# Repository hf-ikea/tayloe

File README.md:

### tayloe downmixer
This is a simple I/Q downmixer intended for use with a soundcard for digitization, with one (very poor) revision created in a weekend, after I discovered the existence of Tayloe detectors online. Created under the influence of music (sumic). Iterations have occured, with the recommended version being the latest commit to this repo. As of writing, however, the design has not been tested in real world (but shall eventually be). The current (and likely forever) design uses a FT232H communicating over I2C to a Si5351A that is then used in a divide-by-four to create the I/Q paired LO, fed into the multiplexer. On the front end is a simple elliptical LPF with a ~30MHz rolloff, and a 1.8V bias circuit. The sample capacitors are of value 0.068uF, which are on the input of an ADA4084 operational amplifier. This is connected through bypass capacitors to the 3.5mm audio jack. For simplicity, a single rail supply is used for the operational amplifier, as the bias on the input should maintain a proper swing.\
"Inspired" by the classic "A Software Defined Radio for the Masses" Series, published in QEX (and available in this repo).\
Hardware is licensed under CERN Open Hardware Licence Version 2 - Strongly Reciprocal (LICENSE.txt)

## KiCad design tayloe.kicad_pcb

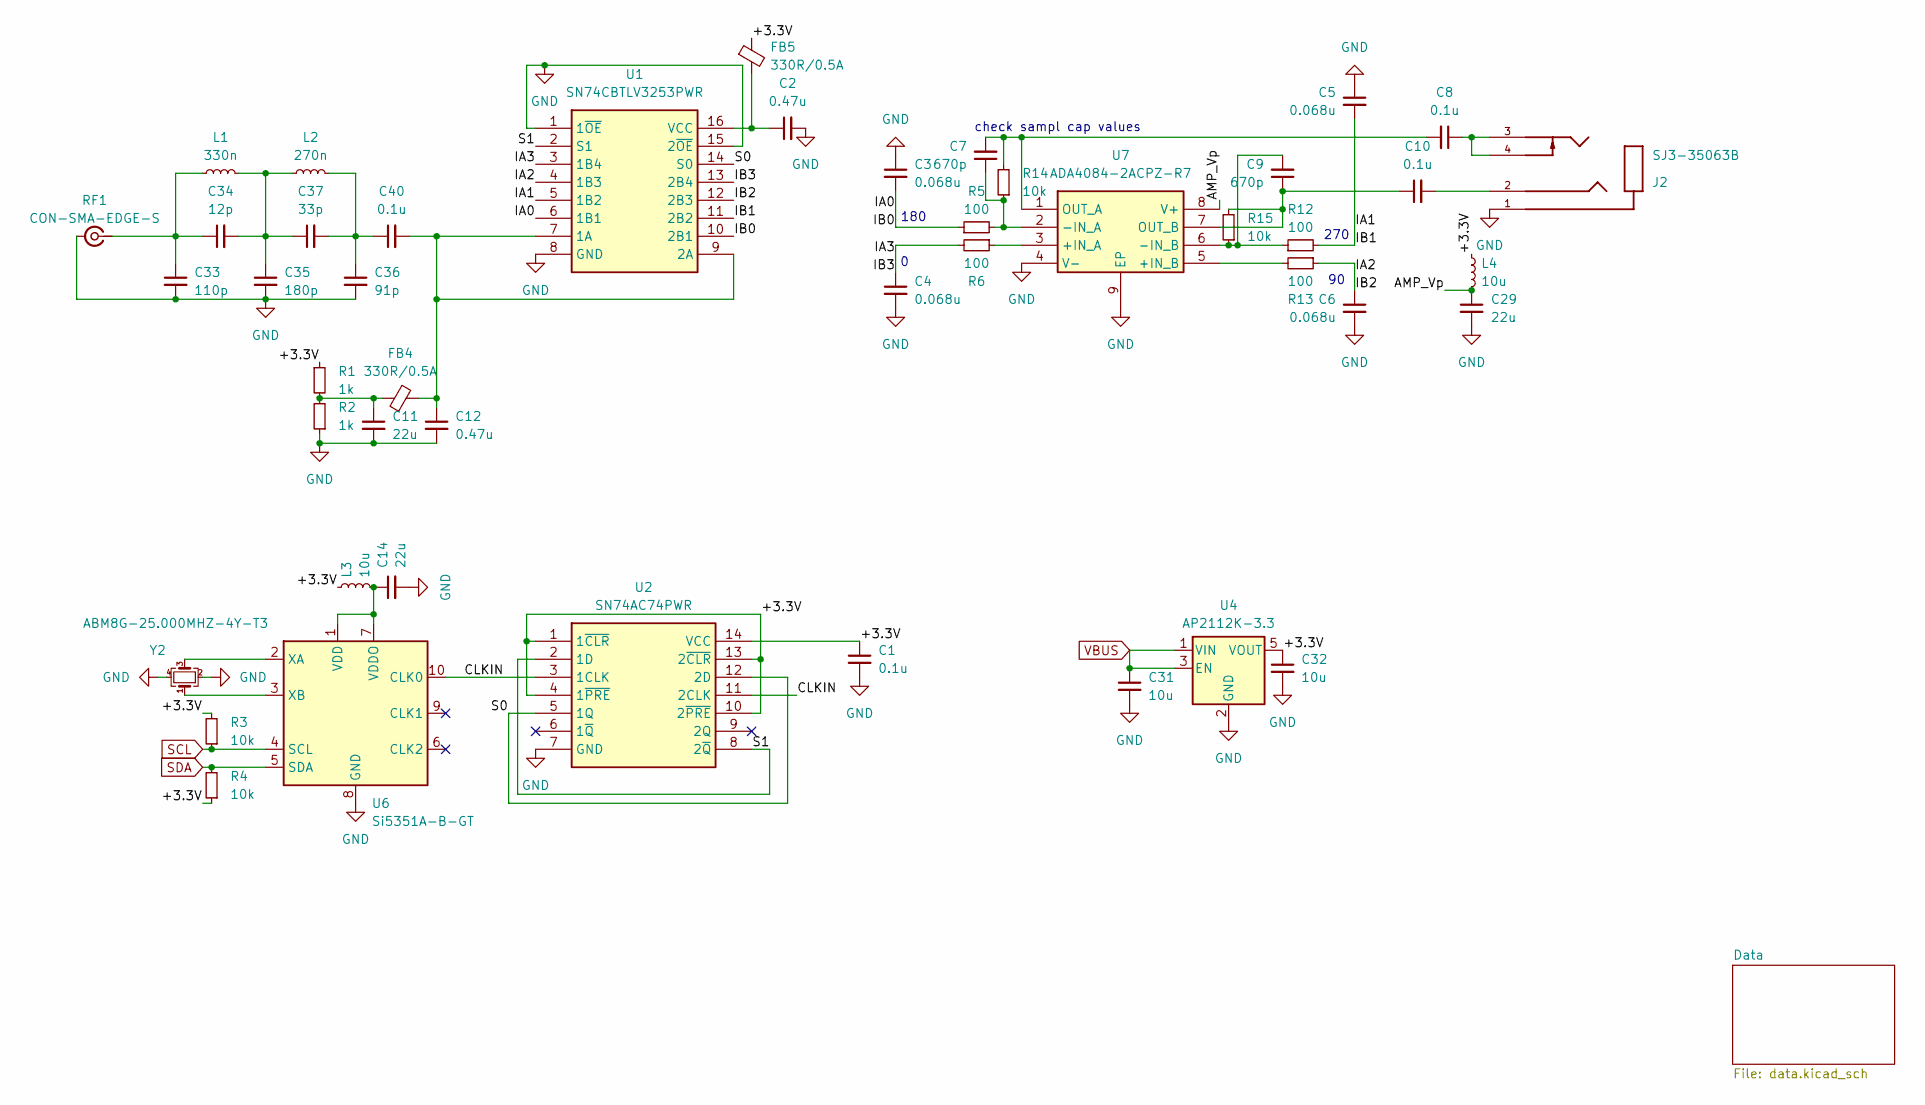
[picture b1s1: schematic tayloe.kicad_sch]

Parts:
C1, C8, C10, C40: 0.1u; C_0603_1608Metric
C2, C12: 0.47u; C_0603_1608Metric
C3, C4, C5, C6: 0.068u; C_0603_1608Metric; Mouser Part 603-CC603JRX7R8BB683
C7, C9: 670p; C_0603_1608Metric; Mouser Part 603-CC603JRX7R8BB683
C11, C14, C29: 22u; C_0603_1608Metric
C31, C32: 10u; C_0603_1608Metric
C33: 110p; C_0603_1608Metric
C34: 12p; C_0603_1608Metric
C35: 180p; C_0603_1608Metric
C36: 91p; C_0603_1608Metric
C37: 33p; C_0603_1608Metric
FB4, FB5: 330R/0.5A; L_0603_1608Metric; Mouser Part 81-BLM18HK331SN1
J2: SJ3-35063B; SAMESKY_SJ3-35063B; PARTREV 1.0
L1: 330n; L_0603_1608Metric
L2: 270n; L_0603_1608Metric
L3, L4: 10u; L_0603_1608Metric
R1, R2: 1k; R_0603_1608Metric
R3, R4, R14, R15: 10k; R_0603_1608Metric
R5, R6, R12, R13: 100; R_0603_1608Metric
RF1: CON-SMA-EDGE-S; SMA_Amphenol_132289_EdgeMount
U1: SN74CBTLV3253PWR; TSSOP-16_4.4x5mm_P0.65mm; Mouser Part 595-SN74CBTLV3253PWR
U2: SN74AC74PWR; TSSOP-14_4.4x5mm_P0.65mm; Mouser Part Number 595-SN74AC74PWR
U4: AP2112K-3.3; SOT-23-5
U6: Si5351A-B-GT; MSOP-10_3x3mm_P0.5mm
U7: ADA4084-2ACPZ-R7; LFCSP-8-1EP_3x3mm_P0.5mm_EP1.6x2.34mm_ThermalVias; Mouser Part 584-ADA4084-2ACPZ-R7
Y2: ABM8G-25.000MHZ-4Y-T3; Crystal_SMD_Abracon_ABM8G-4Pin_3.2x2.5mm

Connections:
/+3.3V: C1.1, C32.1, FB5.1, L3.1, L4.1, R1.1, R3.2, R4.1, U2.1 (1~CLR), U2.4 (1~PRE), U2.10 (2~PRE), U2.13 (2~CLR), U2.14 (VCC), U4.5 (VOUT)
/AMP_Vp: C29.1, L4.2, U7.8 (V+)
/CLKIN: U2.3 (1CLK), U2.11 (2CLK), U6.10 (CLK0)
/IA0: C3.2, R5.1, U1.6 (1B1), U1.10 (2B1)
/IA1: C5.2, R12.2, U1.5 (1B2), U1.11 (2B2)
/IA2: C6.1, R13.1, U1.4 (1B3), U1.12 (2B3)
/IA3: C4.1, R6.2, U1.3 (1B4), U1.13 (2B4)
/S0: U1.14 (S0), U2.5 (1Q), U2.12 (2D)
/S1: U1.2 (S1), U2.2 (1D), U2.8 (2~Q)
GND: C1.2, C2.2, C3.1, C4.2, C5.1, C6.2, C11.2, C12.2, C14.2, C29.2, C31.2, C32.2, C33.2, C35.2, C36.2, J2.1, R2.1, RF1.2 (Ext), U1.1 (1~OE), U1.8 (GND), U1.15 (2~OE), U2.7 (GND), U4.2 (GND), U6.8 (GND), U7.4 (V-), U7.9 (EP), Y2.2, Y2.4; also elsewhere on the board
unnamed: C8.1, J2.3, J2.4
unnamed: C10.2, J2.2
unnamed: C11.1, FB4.1, R1.2, R2.2
unnamed: C34.2, C35.1, C37.1, L1.2, L2.1
unnamed: C36.1, C37.2, C40.1, L2.2
unnamed: C33.1, C34.1, L1.1, RF1.1 (In)
unnamed: C12.1, C40.2, FB4.2, U1.7 (1A), U1.9 (2A)
unnamed: C2.1, FB5.2, U1.16 (VCC)
unnamed: C14.1, L3.2, U6.1 (VDD), U6.7 (VDDO)
unnamed: U6.2 (XA), Y2.3
unnamed: U6.3 (XB), Y2.1
unnamed: R6.1, U7.3 (+IN_A)
unnamed: R13.2, U7.5 (+IN_B)
unnamed: C7.1, R5.2, R14.1, U7.2 (-IN_A)
unnamed: C9.2, R12.1, R15.1, U7.6 (-IN_B)
unnamed: C7.2, C8.2, R14.2, U7.1 (OUT_A)
unnamed: C9.1, C10.1, R15.2, U7.7 (OUT_B)
SCL: R3.1, U6.4 (SCL); also elsewhere on the board
SDA: R4.2, U6.5 (SDA); also elsewhere on the board
VBUS: C31.1, U4.1 (VIN), U4.3 (EN); also elsewhere on the board

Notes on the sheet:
check sampl cap values
270
180

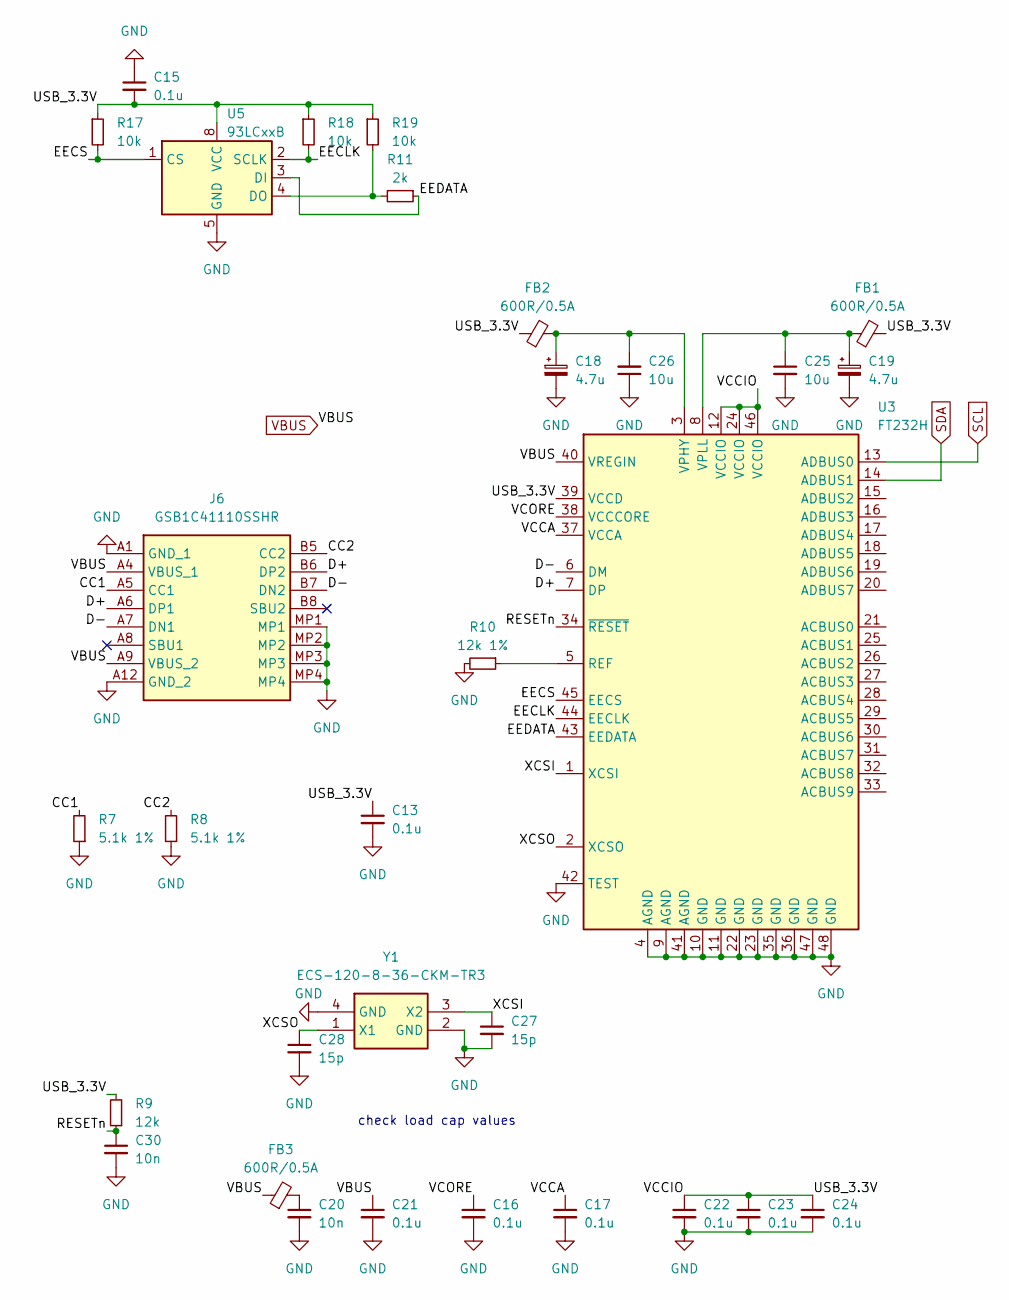
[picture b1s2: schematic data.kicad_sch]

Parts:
C13, C15, C16, C17, C21, C22, C23, C24: 0.1u; C_0603_1608Metric
C18, C19: 4.7u; CP_Elec_5x5.3
C20, C30: 10n; C_0603_1608Metric
C25, C26: 10u; C_0603_1608Metric
C27, C28: 15p; C_0603_1608Metric
FB1, FB2, FB3: 600R/0.5A; L_0603_1608Metric; Mouser Part 81-BLM18HK601SN1D
J6: GSB1C41110SSHR; Manufacturer_Part_Number GSB1C41110SSHR
R7, R8: 5.1k 1%; R_0603_1608Metric
R9: 12k; R_0603_1608Metric
R10: 12k 1%; R_0603_1608Metric
R11: 2k; R_0603_1608Metric
R17, R18, R19: 10k; R_0603_1608Metric
U3: FT232H; LQFP-48_7x7mm_P0.5mm
U5: 93LCxxB; SOIC-8_3.9x4.9mm_P1.27mm
Y1: ECS-120-8-36-CKM-TR3; ECS120836CKMTR3; Mouser Part 520-120-8-36-CKM-TR3

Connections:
/Data/CC1: J6.A5 (CC1), R7.2
/Data/CC2: J6.B5 (CC2), R8.2
/Data/D+: J6.A6 (DP1), J6.B6 (DP2), U3.7 (DP)
/Data/D-: J6.A7 (DN1), J6.B7 (DN2), U3.6 (DM)
/Data/EECLK: R18.2, U3.44 (EECLK), U5.2 (SCLK)
/Data/EECS: R17.2, U3.45 (EECS), U5.1 (CS)
/Data/EEDATA: R11.1, U3.43 (EEDATA), U5.3 (DI)
/Data/RESETn: C30.1, R9.1, U3.34 (~RESET)
/Data/USB_3.3V: C13.1, C15.2, C22.1, C23.1, C24.1, FB1.2, FB2.1, R9.2, R17.1, R18.1, R19.1, U3.12 (VCCIO), U3.24 (VCCIO), U3.39 (VCCD), U3.46 (VCCIO), U5.8 (VCC)
/Data/VCCA: C17.1, U3.37 (VCCA)
/Data/VCORE: C16.1, U3.38 (VCCCORE)
/Data/XCSI: C27.1, U3.1 (XCSI), Y1.3 (X2)
/Data/XCSO: C28.1, U3.2 (XCSO), Y1.1 (X1)
GND: C13.2, C15.1, C16.2, C17.2, C18.2, C19.2, C20.2, C21.2, C22.2, C23.2, C24.2, C25.2, C26.1, C27.2, C28.2, C30.2, J6.A1 (GND_1), J6.A12 (GND_2), J6.MP1, J6.MP2, J6.MP3, J6.MP4, R7.1, R8.1, R10.2, U3.4 (AGND), U3.9 (AGND), U3.10 (GND), U3.11 (GND), U3.22 (GND), U3.23 (GND), U3.35 (GND), U3.36 (GND), U3.41 (AGND), U3.42 (TEST), U3.47 (GND), U3.48 (GND), U5.5 (GND), Y1.2 (GND), Y1.4 (GND); also elsewhere on the board
unnamed: C20.1, FB3.2
unnamed: R10.1, U3.5 (REF)
unnamed: C18.1, C26.2, FB2.2, U3.3 (VPHY)
unnamed: C19.1, C25.1, FB1.1, U3.8 (VPLL)
unnamed: R11.2, R19.2, U5.4 (DO)
SCL: U3.13 (ADBUS0); also elsewhere on the board
SDA: U3.14 (ADBUS1); also elsewhere on the board
VBUS: C21.1, FB3.1, J6.A4 (VBUS_1), J6.A9 (VBUS_2), U3.40 (VREGIN); also elsewhere on the board

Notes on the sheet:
check load cap values

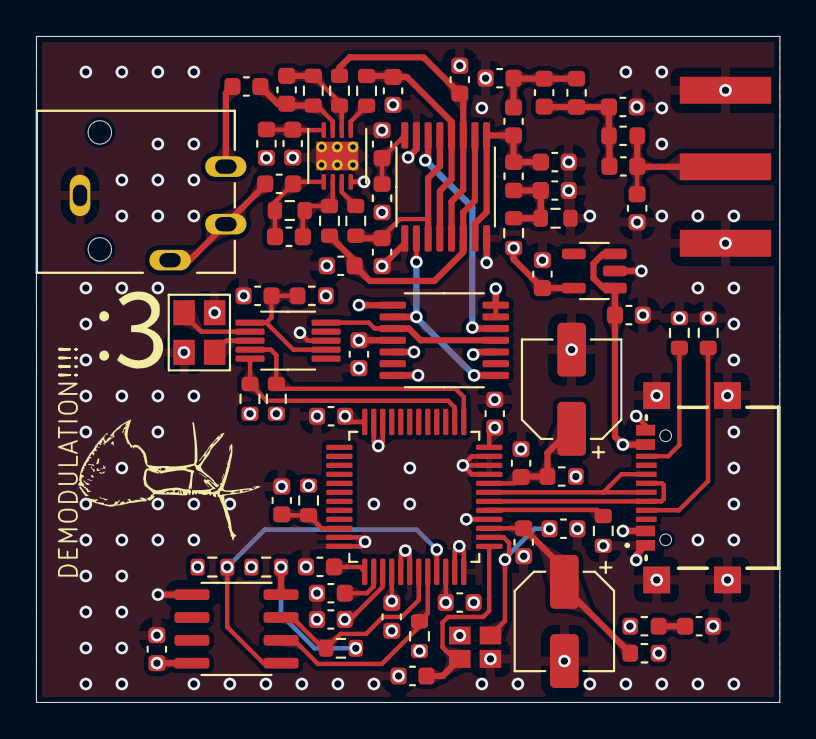
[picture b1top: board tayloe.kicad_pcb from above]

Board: 4 copper layers, 41.3 x 37.0 mm, 78 parts (0 on the bottom side), 48 nets.

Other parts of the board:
G**: bird

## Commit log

2025-02-18 first version
2025-02-19 whatever
2025-02-26 rev 2
2025-03-02 save
2025-03-03 rev 3
2025-03-04 remove file
2025-03-08 rev 3.1
2025-03-08 remove lck file
2025-03-08 i forgor via stiching (rev 3.2) (for real this time)
